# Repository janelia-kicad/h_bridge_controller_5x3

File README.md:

# h_bridge_controller_5x3

Authors:

    Peter Polidoro <polidorop@janelia.hhmi.org>

License:

    BSD

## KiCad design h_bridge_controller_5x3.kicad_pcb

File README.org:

#+TITLE: h_bridge_controller_5x3
#+AUTHOR: Peter Polidoro
#+EMAIL: peter@polidoro.io

* Repository Information
  - Author :: Peter Polidoro
  - License :: Open-Source Hardware

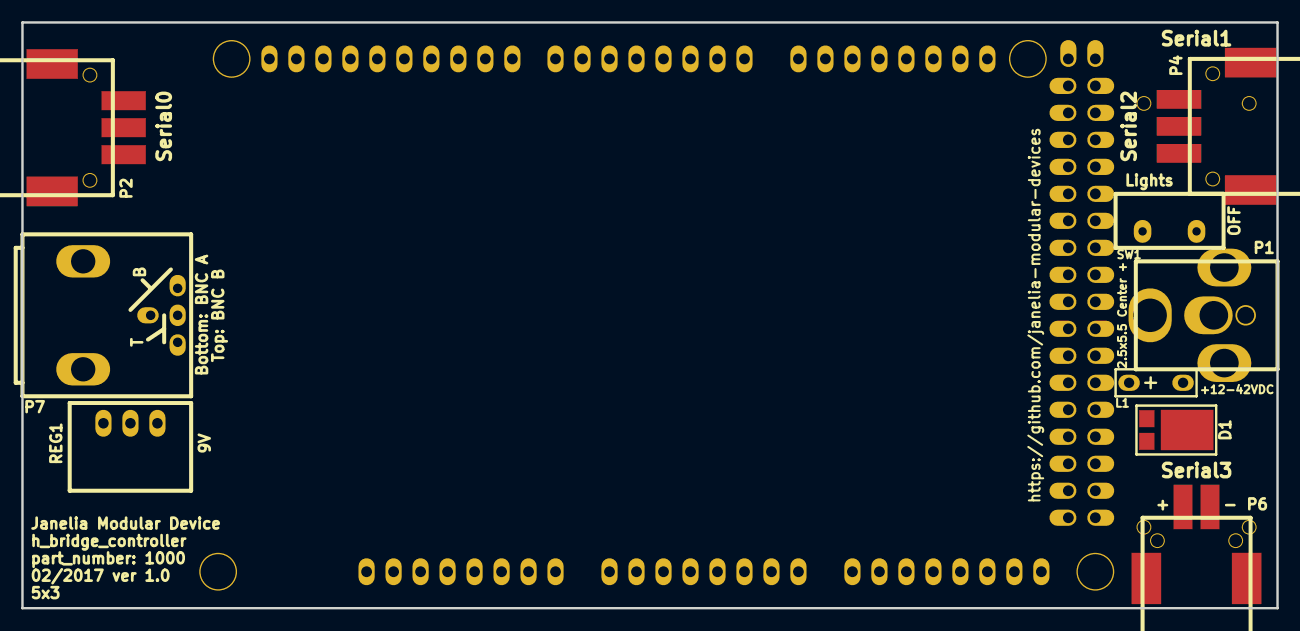
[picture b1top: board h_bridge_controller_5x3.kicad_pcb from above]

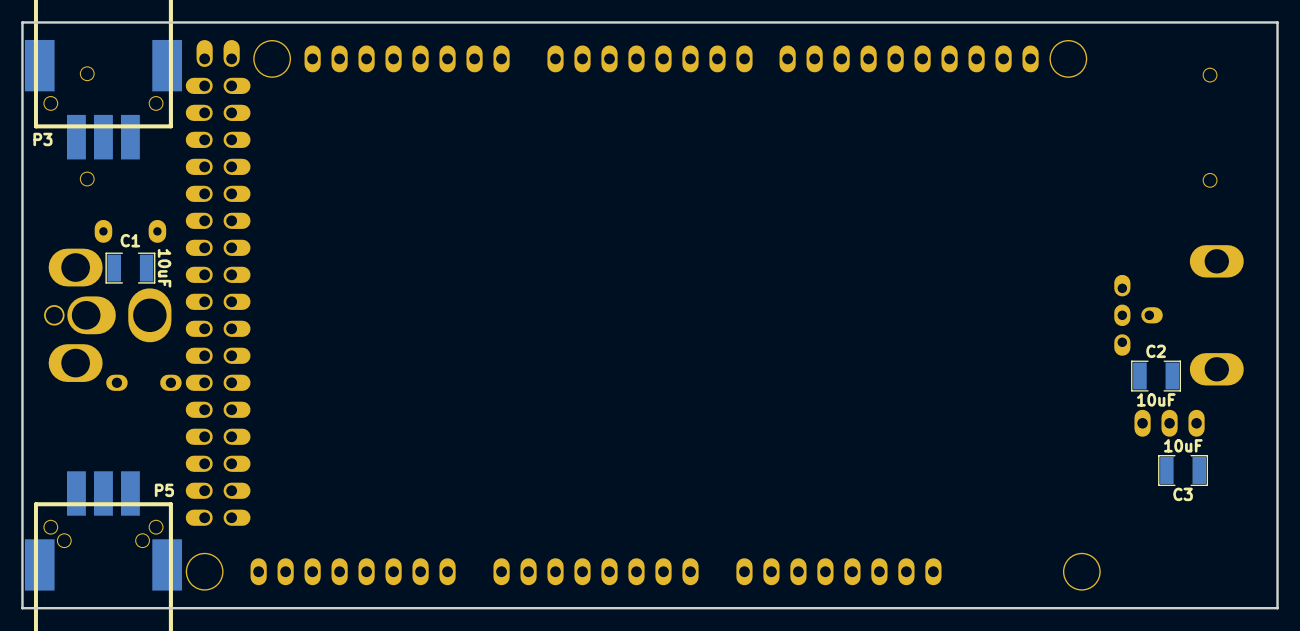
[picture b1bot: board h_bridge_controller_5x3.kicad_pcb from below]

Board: 2 copper layers, 118.1 x 55.1 mm, 15 parts (5 on the bottom side), 15 nets, no tracks yet.

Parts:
ARDUINO1: ARDUINO_MEGA; ARDUINO_MEGA_SHIELD
C1, C2, C3: 10uF; SM1210
D1: diode_schottky_45V_10A; CFP15
L1: LED_24V; LED_555-3XXX
P1: PWR_JACK_2.5x5.5; DCJACK_2PIN_HIGHCURRENT
P2, P3, P4, P5: HEADER_01X03_SMD_RA; Header_3_Pin_SMD_RA
P6: HEADER_01X02_SMD_RA; Header_2_Pin_SMD_RA
P7: BNC_DOUBLE_RA; BNC_DOUBLE
REG1: CONV_DC_DC_9V_1A; DC_DC_CONV_R78C
SW1: SPST_SLIDE_AS

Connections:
/BNC_A: ARDUINO1.2, P7.1
/BNC_B: ARDUINO1.3, P7.3
/LED_GND: L1.2, SW1.3
/RX0: ARDUINO1.0, P2.1
/RX1: ARDUINO1.19, P3.1
/RX2: ARDUINO1.17, P4.1
/RX3: ARDUINO1.15, P5.1
/TX0: ARDUINO1.1, P2.3
/TX1: ARDUINO1.18, P3.3
/TX2: ARDUINO1.16, P4.3
/TX3: ARDUINO1.14, P5.3
/V_IN: ARDUINO1.V_IN, C3.1, REG1.3
GND: ARDUINO1.GND1, ARDUINO1.GND2, C1.2, C2.2, C3.2, P1.2, P2.2, P3.2, P4.2, P5.2, P6.1, P7.2, P7.4, REG1.2, SW1.1
VAA: C1.1, C2.1, D1.2, L1.1, P1.1, REG1.1
VCC: D1.1, P6.2

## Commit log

2017-01-24 Initial commit.
2017-02-02 Added template files.
2017-03-24 Updated documentation.
2017-06-15 Removed .cmp file.
2017-09-22 Removed extra libraries.
2018-01-08 Updated to v4.
2018-01-08 Added v4 files.
2018-01-08 Updated gitignore.
2018-03-09 Update license from software to hardware.
2018-04-12 README.md -> README.org.
2018-04-19 Added .DS_Store to .gitignore.
2018-05-16 Added generate_kicad_documentation submodule.
2018-05-17 Updated submodules.
2018-08-12 Removed v4 files.
2018-08-24 Removed F.SilkS from pads.
2018-08-27 Removed *.SilkS from pads.
2021-09-16 Update email address
2021-09-21 Remove ignored files
2022-02-22 Add guix files
2022-02-23 Add guix documentation
